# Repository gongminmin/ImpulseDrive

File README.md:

# Impulse Drive

In Star Trek universe, impulse drive is a propulsion system of spacecrafts for interplanetary travel. This project is trying to design a real-world impulse drive. The basic characteristics of this engine are

* Electric propulsion
* Large thrust
* Long specific impulse
* No or little moving parts
* Good scalability
* Low cost

We'd like to make it easy to implement, so people can build it as a hobby project.

NOTE: Please turn on git LFS when cloning this project.

## Method

There are many different engine designs for spacecraft propulsion, check [wikipedia](https://en.wikipedia.org/wiki/Spacecraft_propulsion#Table_of_methods) for a list. The only one design among them that fits these requirements is magnetoplasmadynamic thruster, a.k.a, MPDT or MPD thruster. More details in [MPD](Doc/Mpd.md).

Our design is based on MPDT, with several significant improvements.

## Design

The principle of our design, and a detailed introduction of modules are in [Design](Doc/Design.md)

## Disclaimer

MPD thruster is operated by **LETHALLY** high voltage and current. If you don't have enough knowledge and experiences on high voltage electric, please keep extreme cautions on insulation.

## Directories

* Circuit folder is the electric design of the system. The files can be open by [KiCad](https://kicad-pcb.org/)
* 3DModel folder is the 3D model design of some components. It's in [Blender](https://www.blender.org/) format.
* Doc folder contains some documents

## License

ImpulseDrive is distributed under the terms of MIT License. See [LICENSE](LICENSE) for details.

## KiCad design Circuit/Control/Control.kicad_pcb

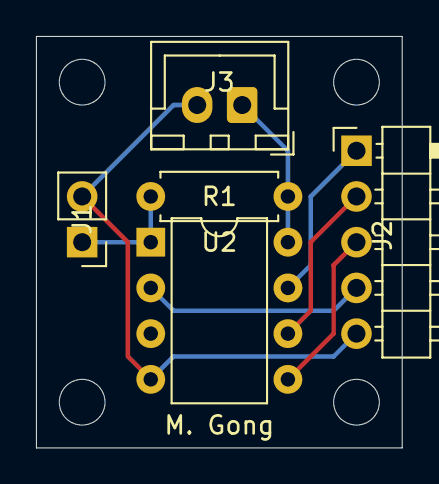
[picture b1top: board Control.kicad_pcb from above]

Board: 2 copper layers, 20.3 x 22.9 mm, 5 parts (0 on the bottom side), 7 nets.

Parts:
J1: Signal; PinHeader_1x02_P2.54mm_Vertical
J2: To Switch; PinHeader_1x05_P2.54mm_Horizontal
J3: Power; JST_XH_B2B-XH-A_1x02_P2.50mm_Vertical
R1: 3.3K; R_Axial_DIN0207_L6.3mm_D2.5mm_P7.62mm_Horizontal
U2: ATtiny85-20PU; DIP-8_W7.62mm

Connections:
+5V: J3.1, R1.1, U2.8
/CapacitorSignal: J2.4, U2.2
/CoilSignal: J2.1, U2.7
/ControlSignal: J1.1, R1.2, U2.1
/PropellantInjectorSignal: J2.3, U2.5
/StarterSignal: J2.2, U2.6
GND: J1.2, J2.5, J3.2, U2.4

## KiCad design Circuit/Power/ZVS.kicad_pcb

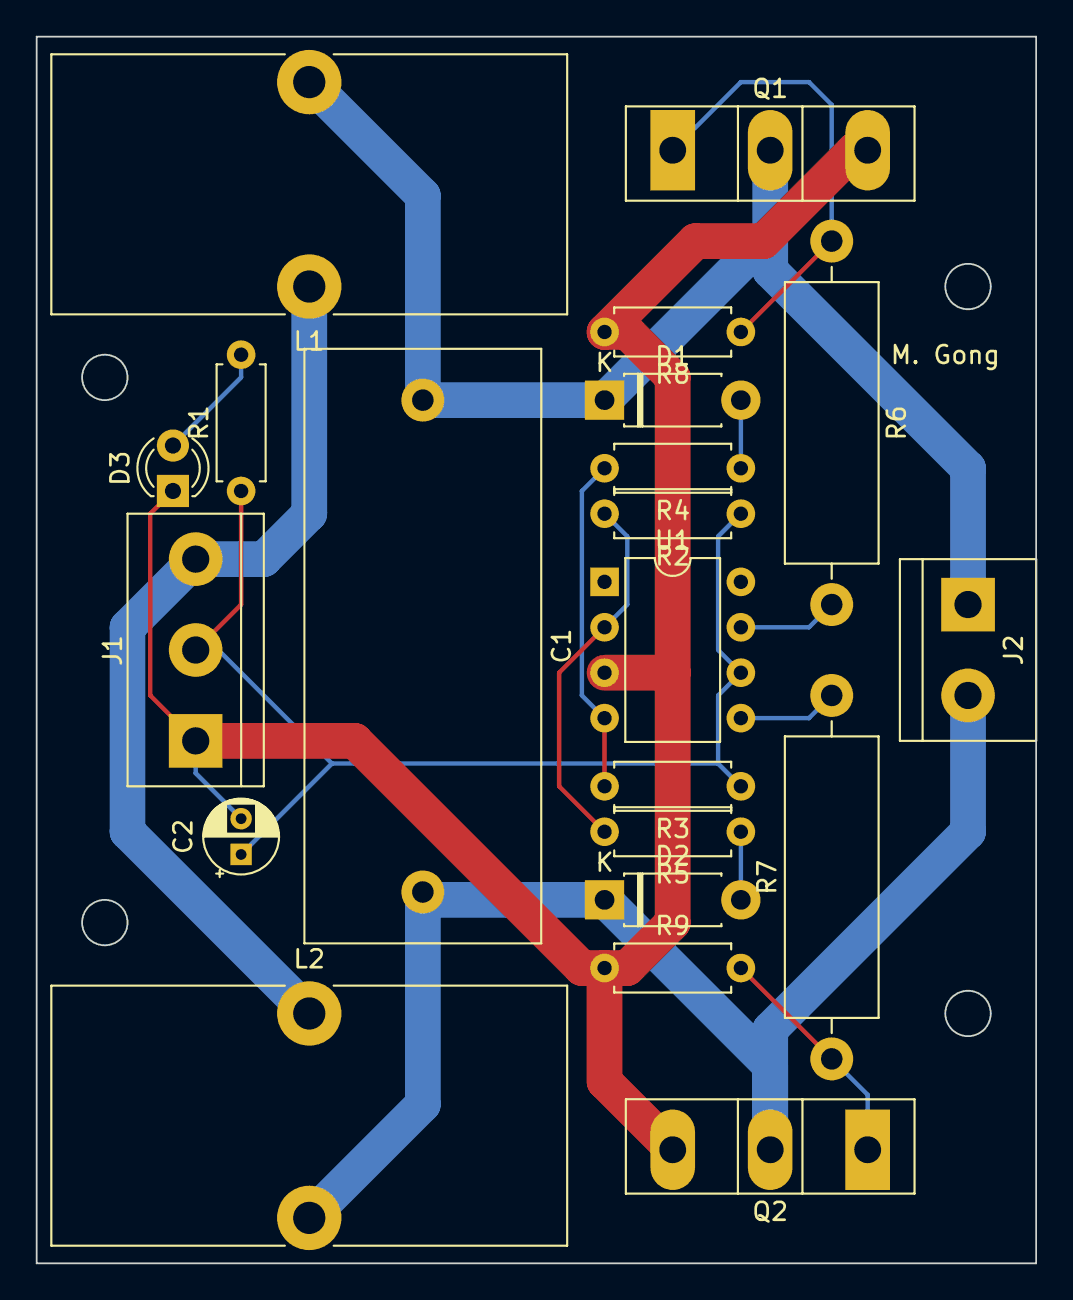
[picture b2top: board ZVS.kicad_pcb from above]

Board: 2 copper layers, 55.9 x 68.6 mm, 21 parts (0 on the bottom side), 14 nets.

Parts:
C1: MKP 0.33uF; C_Rect_L33.0mm_W13.0mm_P27.50mm_MKS4
C2: 10uF; CP_Radial_D4.0mm_P2.00mm
D1, D2: UF4007; D_DO-41_SOD81_P7.62mm_Horizontal
D3: LED; LED_D3.0mm_FlatTop
J1: 12V DC in; TerminalBlock_bornier-3_P5.08mm
J2: Output; TerminalBlock_bornier-2_P5.08mm
L1, L2: 100uH; L_Toroid_Vertical_L28.6mm_W14.3mm_P11.43mm_Bourns_5700
Q1, Q2: IRFP250; TO-247-3_Vertical
R1: 2.2K; R_Axial_DIN0207_L6.3mm_D2.5mm_P7.62mm_Horizontal
R2, R3: 3.3K; R_Axial_DIN0207_L6.3mm_D2.5mm_P7.62mm_Horizontal
R4, R5: 100; R_Axial_DIN0207_L6.3mm_D2.5mm_P7.62mm_Horizontal
R6, R7: 10R 5W; R_Axial_DIN0516_L15.5mm_D5.0mm_P20.32mm_Horizontal
R8, R9: 10K; R_Axial_DIN0207_L6.3mm_D2.5mm_P7.62mm_Horizontal
U1: UCC27524P; DIP-8_W7.62mm

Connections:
/DCInput+: C2.1, J1.2, R1.1, R2.1, R3.1, U1.6
/Output+: C1.1, D1.1, J2.1, L1.2, Q1.2
/Output-: C1.2, D2.1, J2.2, L2.2, Q2.2
GND: C2.2, D3.1, J1.1, Q1.3, Q2.3, R8.2, R9.1, U1.3
unnamed: D1.2, R4.1
unnamed: D2.2, R5.1
unnamed: D3.2, R1.2
unnamed: J1.3, L1.1, L2.1
unnamed: Q1.1, R6.1, R8.1
unnamed: Q2.1, R7.1, R9.2
unnamed: R2.2, R5.2, U1.2
unnamed: R3.2, R4.2, U1.4
unnamed: R6.2, U1.7
unnamed: R7.2, U1.5

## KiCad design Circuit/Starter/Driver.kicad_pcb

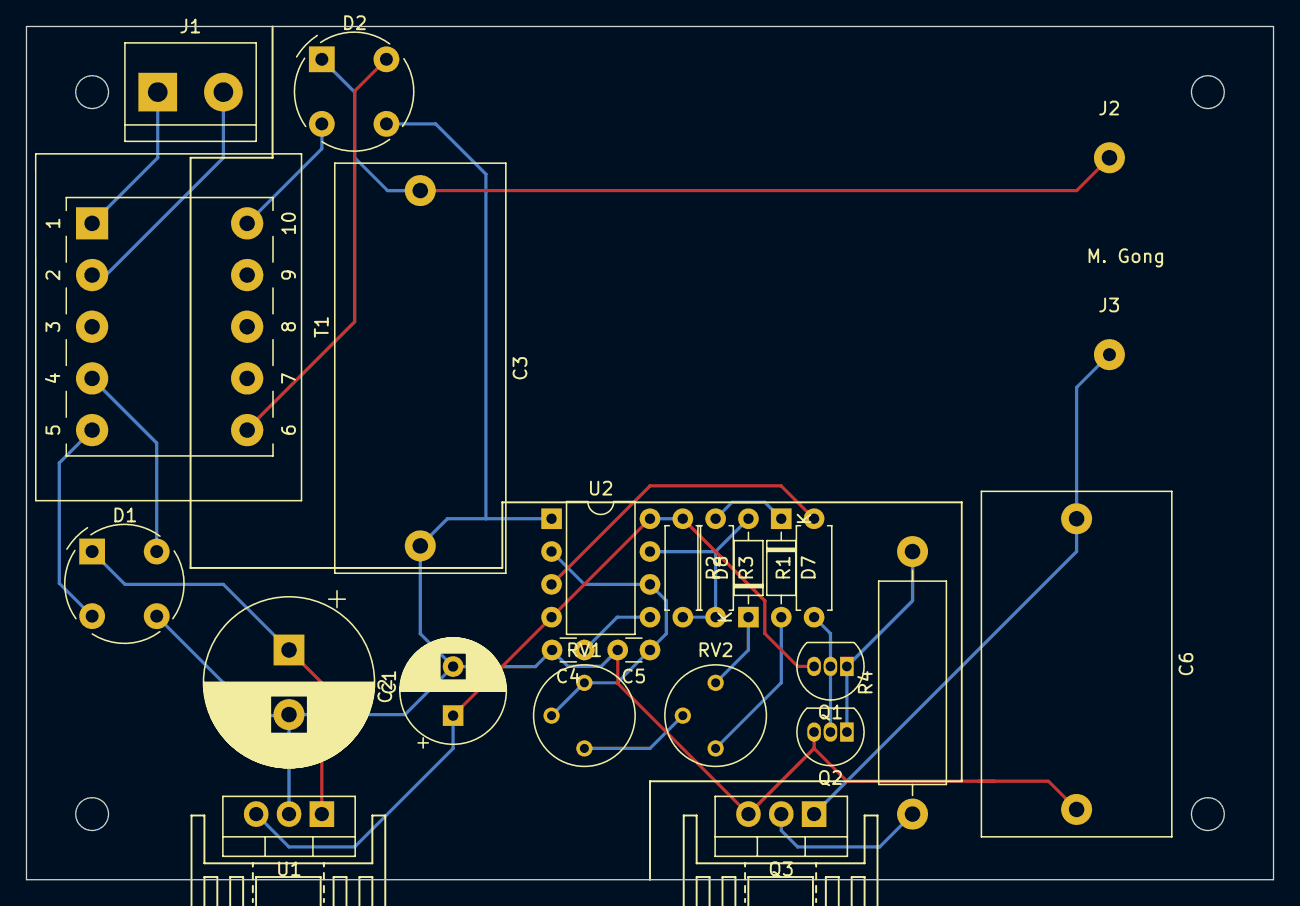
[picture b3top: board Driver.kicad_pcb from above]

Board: 2 copper layers, 96.5 x 66.0 mm, 27 parts (0 on the bottom side), 22 nets.

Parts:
C1: 2200uF; CP_Radial_D13.0mm_P5.00mm
C2: 1000uF; CP_Radial_D8.0mm_P3.80mm
C3: MKP 1uF 275V; C_Rect_L31.5mm_W13.0mm_P27.50mm_MKS4
C4: 0.01uF; C_Disc_D3.0mm_W1.6mm_P2.50mm
C5: 330pF; C_Disc_D3.0mm_W1.6mm_P2.50mm
C6: 0.01uF 2kV; C_Rect_L26.5mm_W15mm_P22.50mm_MKS4
D1, D2: 2W10; Diode_Bridge_Round_D9.0mm
D7, D8: 1N4148; D_DO-35_SOD27_P7.62mm_Horizontal
HS1, HS2: Heatsink; Heatsink_TO220_15x10mm
J1: AC Power; TerminalBlock_bornier-2_P5.08mm
J2: To Output Transformer+; SolderWirePad_1x01_Drill1.2mm
J3: To Output Transformer-; SolderWirePad_1x01_Drill1.2mm
Q1: 2N3904; TO-92_Inline
Q2: 2N3906; TO-92_Inline
Q3: FCPF220N80; TO-220-3_Vertical
R1: 270; R_Axial_DIN0207_L6.3mm_D2.5mm_P7.62mm_Horizontal
R2, R3: 1K; R_Axial_DIN0207_L6.3mm_D2.5mm_P7.62mm_Horizontal
R4: 10R 5W; R_Axial_DIN0516_L15.5mm_D5.0mm_P20.32mm_Horizontal
RV1, RV2: 5K; Potentiometer_Bourns_3339P_Vertical
T1: 6:6:50; Transformer_Generic_EE25_10Pin
U1: L7812; TO-220-3_Vertical
U2: NE555; DIP-8_W7.62mm

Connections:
+12V: C2.1, Q1.3, R2.1, U1.3, U2.4, U2.8
/PowerIn+: J1.1, T1.1
/PowerIn-: J1.2, T1.2
/ToOutputTransformer+: C3.1, D2.1, J2.1
/ToOutputTransformer-: C6.1, J3.1, Q3.1
GND: C1.2, C2.2, C3.2, C4.2, C5.2, C6.2, D1.3, D2.3, Q2.3, Q3.3, U1.2, U2.1
unnamed: C1.1, D1.1, U1.1
unnamed: C4.1, U2.5
unnamed: C5.1, RV1.2, RV1.3, U2.2, U2.6
unnamed: D1.2, T1.5
unnamed: D1.4, T1.4
unnamed: D2.2, T1.10
unnamed: D2.4, T1.6
unnamed: D7.1, R3.1
unnamed: D7.2, RV2.1
unnamed: D8.1, RV2.3
unnamed: D8.2, R2.2, R3.2, U2.7
unnamed: Q1.1, Q2.1, R4.2
unnamed: Q1.2, Q2.2, R1.1
unnamed: Q3.2, R4.1
unnamed: R1.2, U2.3
unnamed: RV1.1, RV2.2

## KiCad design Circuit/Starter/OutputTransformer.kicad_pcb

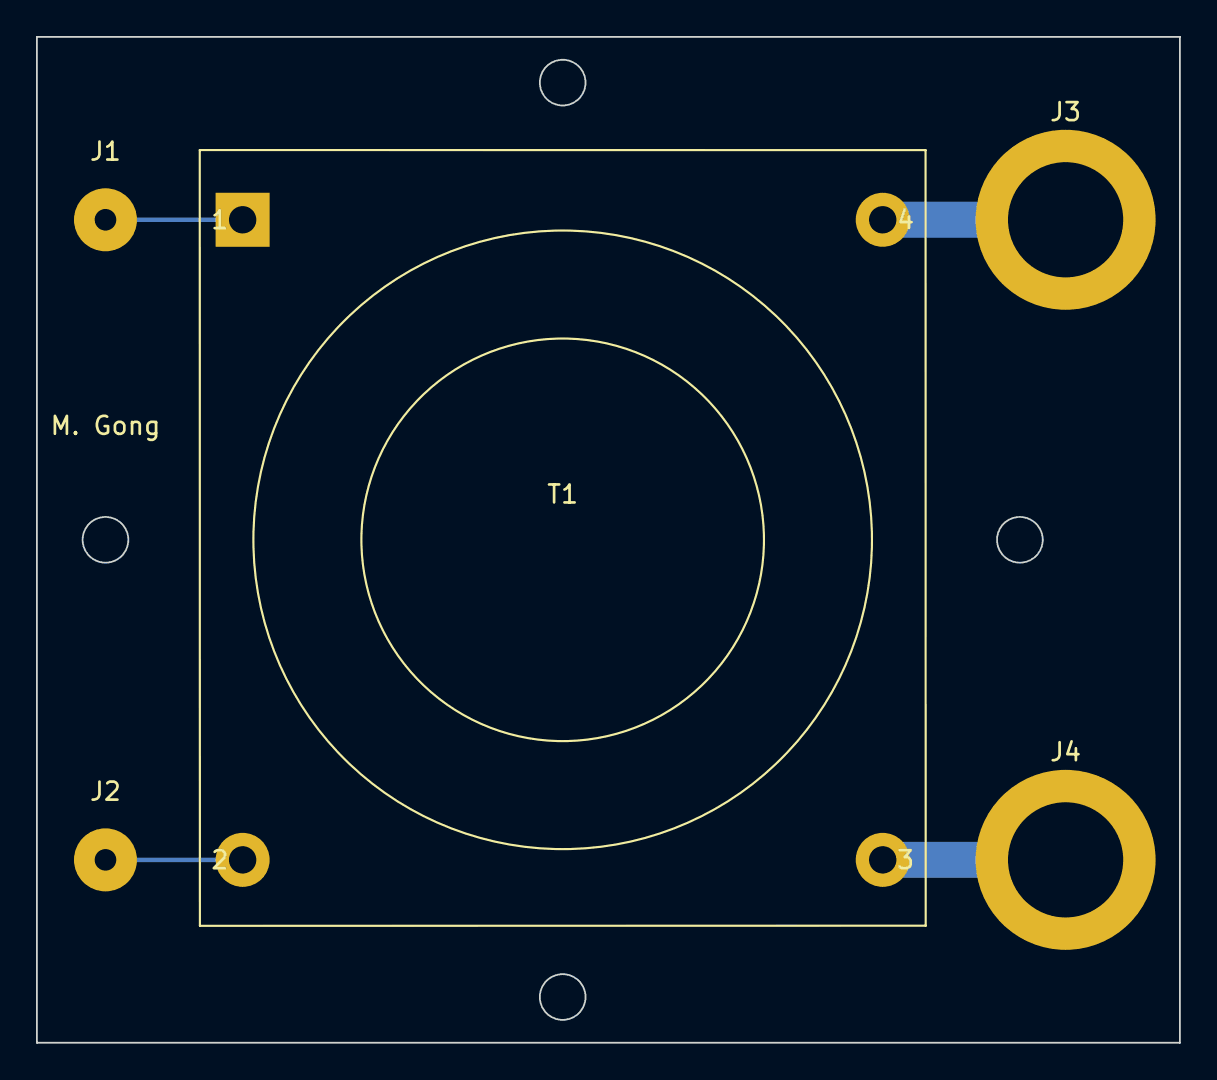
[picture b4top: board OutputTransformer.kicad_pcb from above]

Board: 2 copper layers, 63.5 x 55.9 mm, 5 parts (0 on the bottom side), 4 nets.

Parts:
J1: Input+; SolderWirePad_1x01_Drill1.2mm
J2: Input-; SolderWirePad_1x01_Drill1.2mm
J3: Output+; MountingHole_6.4mm_M6_ISO14580_Pad
J4: Output-; MountingHole_6.4mm_M6_ISO14580_Pad
T1: 3:40 Air Core (primary 0.8uH, 0.225in length, 2in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; Air_Core_Transformer_Vertical_1P_1S

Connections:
/Input+: J1.1, T1.1
/Input-: J2.1, T1.2
/Output+: J3.1, T1.4
/Output-: J4.1, T1.3

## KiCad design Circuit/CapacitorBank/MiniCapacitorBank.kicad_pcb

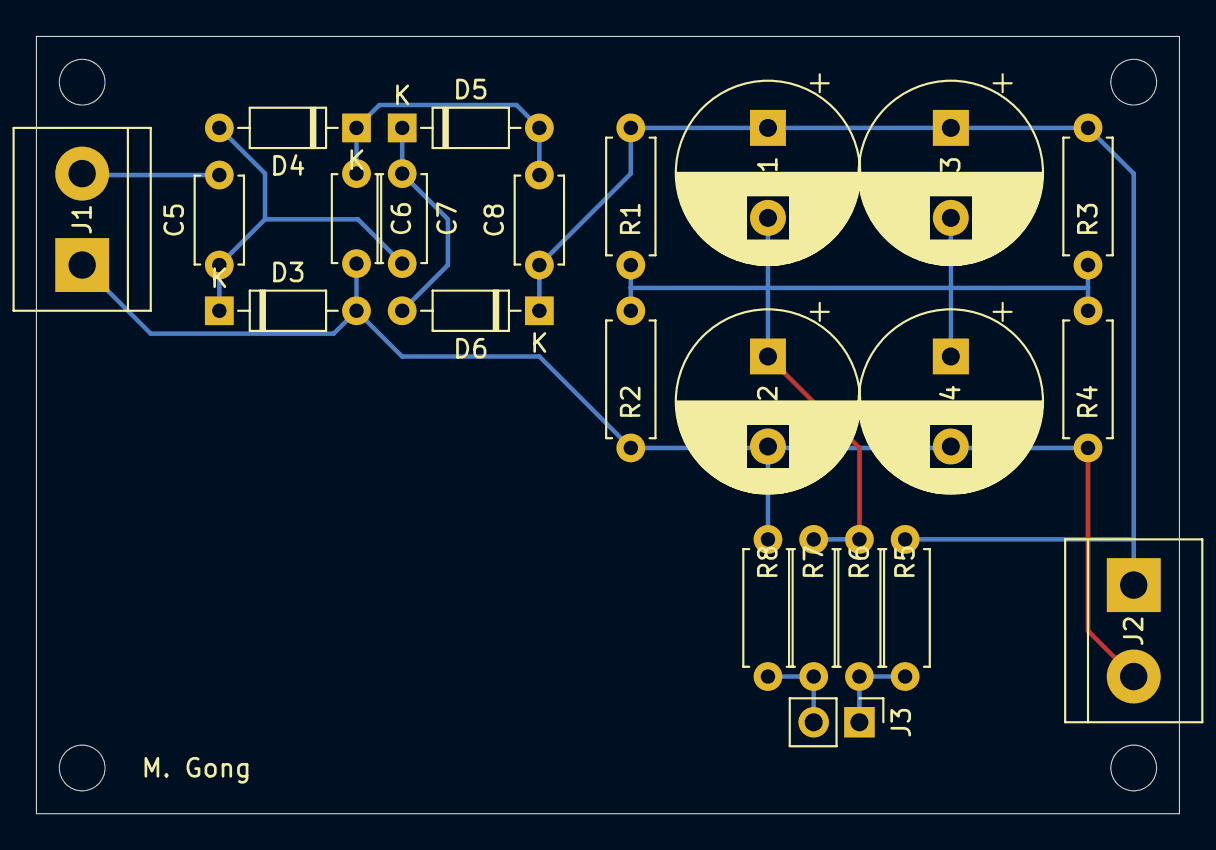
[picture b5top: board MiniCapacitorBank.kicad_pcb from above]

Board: 2 copper layers, 63.5 x 43.2 mm, 23 parts (0 on the bottom side), 9 nets.

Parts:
C1, C2, C3, C4: 330uF/50V; CP_Radial_D10.0mm_P5.00mm
C5, C6, C7, C8: 0.1uF; C_Disc_D4.7mm_W2.5mm_P5.00mm
D3, D4, D5, D6: 1N4148; D_DO-35_SOD27_P7.62mm_Horizontal
J1: AC Power In; TerminalBlock_bornier-2_P5.08mm
J2: 68V out; TerminalBlock_bornier-2_P5.08mm
J3: To Voltage Sensing; PinHeader_1x02_P2.54mm_Vertical
R1, R2, R3, R4: 68K; R_Axial_DIN0207_L6.3mm_D2.5mm_P7.62mm_Horizontal
R5, R8: 1M; R_Axial_DIN0207_L6.3mm_D2.5mm_P7.62mm_Horizontal
R6, R7: 100K; R_Axial_DIN0207_L6.3mm_D2.5mm_P7.62mm_Horizontal

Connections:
/ACPowerIn+: C5.2, J1.2
/ACPowerIn-: C2.2, C4.2, C6.2, D3.2, J1.1, J2.2, R2.2, R4.2, R8.2
/PowerOut+: C1.1, C3.1, C8.1, D6.1, J2.1, R1.1, R3.1, R5.1
/Sensor0V: J3.2, R7.2, R8.1
/Sensor6V: J3.1, R5.2, R6.1
unnamed: C1.2, C2.1, C3.2, C4.1, R1.2, R2.1, R3.2, R4.1, R6.2, R7.1
unnamed: C5.1, C7.2, D3.1, D4.2
unnamed: C6.1, C8.2, D4.1, D5.2
unnamed: C7.1, D5.1, D6.2

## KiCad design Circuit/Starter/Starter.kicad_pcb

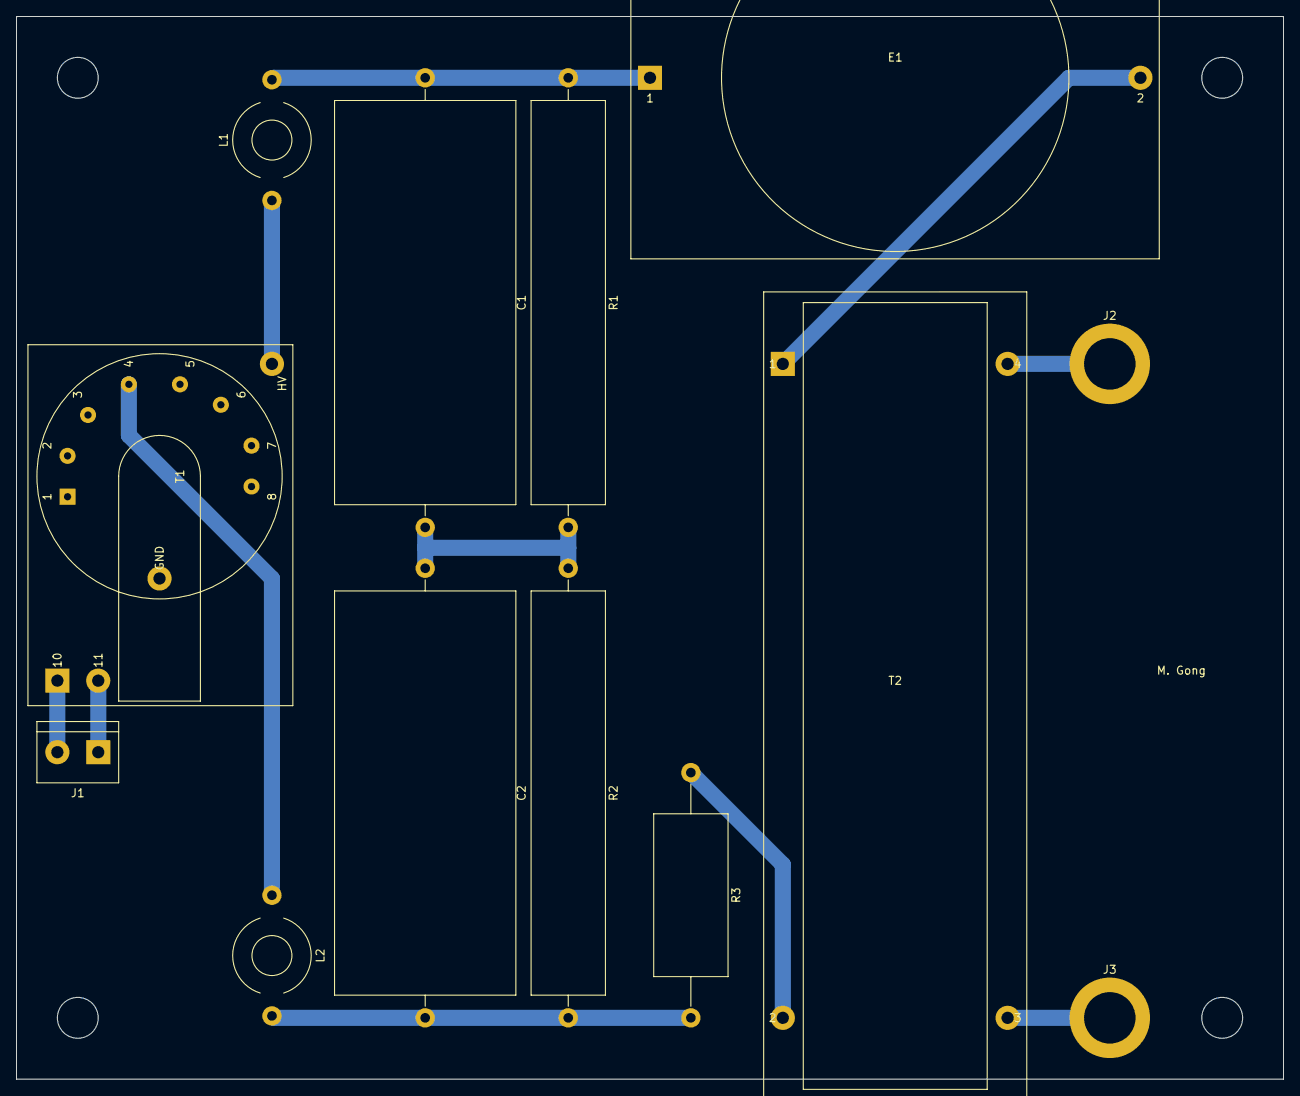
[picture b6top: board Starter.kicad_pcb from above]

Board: 2 copper layers, 157.5 x 132.1 mm, 13 parts (0 on the bottom side), 11 nets.

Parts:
C1, C2: 10nF/8kV; C_Axial_L50.0mm_D23.0mm_P55.0mm_Horizontal
E1: SPARK_GAP 10kV; Spark_Gap
J1: From Power; TerminalBlock_bornier-2_P5.08mm
J2: Output+; MountingHole_6.4mm_M6_ISO14580_Pad
J3: Output-; MountingHole_6.4mm_M6_ISO14580_Pad
L1, L2: 10uH; L_Toroid_Horizontal_D9.5mm_P15.00mm_Diameter10-5mm_Amidon-T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
R1, R2: 100M/5W; R_Axial_Power_L50.0mm_W9.0mm_P55.88mm
R3: 1Ω/10W; R_Axial_DIN0922_L20.0mm_D9.0mm_P30.48mm_Horizontal
T1: BSH12-N406L 8:6400; Flyback_Transformer_BSH12-N406L
T2: 20:20; Air_Core_Transformer_1P_1S

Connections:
/PowerIn+: J1.2, T1.10
/PowerIn-: J1.1, T1.11
/PowerOut+: J2.1, T2.4
/PowerOut-: J3.1, T2.3
unnamed: C1.1, E1.1, L1.2, R1.1
unnamed: C1.2, C2.1, R1.2, R2.1
unnamed: C2.2, L2.2, R2.2, R3.2
unnamed: E1.2, T2.1
unnamed: L1.1, T1.12
unnamed: L2.1, T1.4
unnamed: R3.1, T2.2

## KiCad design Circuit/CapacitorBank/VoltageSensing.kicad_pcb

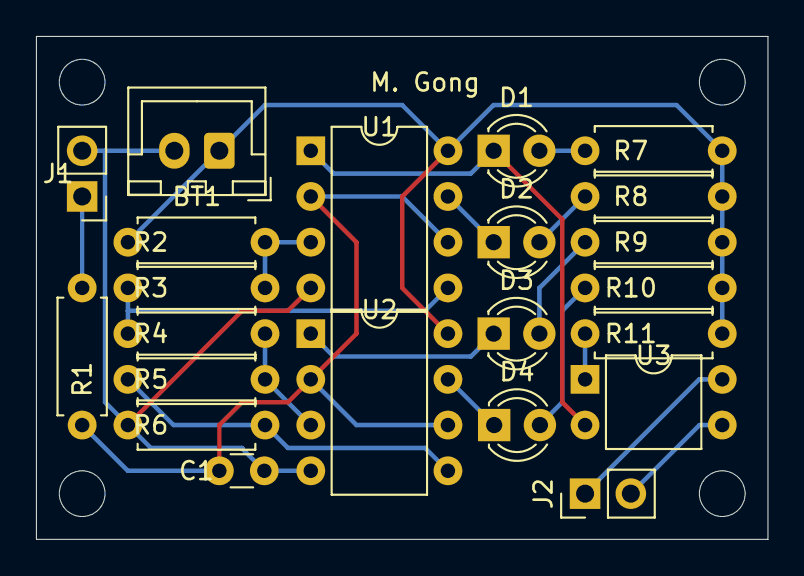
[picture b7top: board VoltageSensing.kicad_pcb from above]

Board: 2 copper layers, 40.6 x 27.9 mm, 22 parts (0 on the bottom side), 19 nets.

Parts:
BT1: 12V Battery; JST_XH_B2B-XH-A_1x02_P2.50mm_Vertical
C1: 0.1uF; C_Disc_D3.0mm_W1.6mm_P2.50mm
D1, D2, D3, D4: LED; LED_D3.0mm_FlatTop
J1: From Capacitor Bank; PinHeader_1x02_P2.54mm_Vertical
J2: To Control; PinHeader_1x02_P2.54mm_Vertical
R1, R11: 1K; R_Axial_DIN0207_L6.3mm_D2.5mm_P7.62mm_Horizontal
R2: 20K; R_Axial_DIN0207_L6.3mm_D2.5mm_P7.62mm_Horizontal
R3, R4, R5, R6: 4.7K; R_Axial_DIN0207_L6.3mm_D2.5mm_P7.62mm_Horizontal
R7, R8, R9, R10: 2.2K; R_Axial_DIN0207_L6.3mm_D2.5mm_P7.62mm_Horizontal
U1, U2: LM393; DIP-8_W7.62mm
U3: PC817; DIP-4_W7.62mm

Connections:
+12V: BT1.1, R2.2, R7.1, R8.1, R9.1, R10.1, R11.1, U1.8, U2.8
/ControlGND: J2.2, U3.3
/ControlSignal: J2.1, U3.4
/Sensor6V: J1.1, R1.2
GND: BT1.2, C1.2, J1.2, R6.1, U1.4, U2.4
unnamed: C1.1, R1.1, U1.2, U1.6, U2.2, U2.6
unnamed: D1.1, U1.1, U3.2
unnamed: D1.2, R7.2
unnamed: D2.1, U1.7
unnamed: D2.2, R8.2
unnamed: D3.1, U2.1
unnamed: D3.2, R9.2
unnamed: D4.1, U2.7
unnamed: D4.2, R10.2
unnamed: R2.1, R3.2, U1.3
unnamed: R3.1, R4.2, U1.5
unnamed: R4.1, R5.2, U2.3
unnamed: R5.1, R6.2, U2.5
unnamed: R11.2, U3.1

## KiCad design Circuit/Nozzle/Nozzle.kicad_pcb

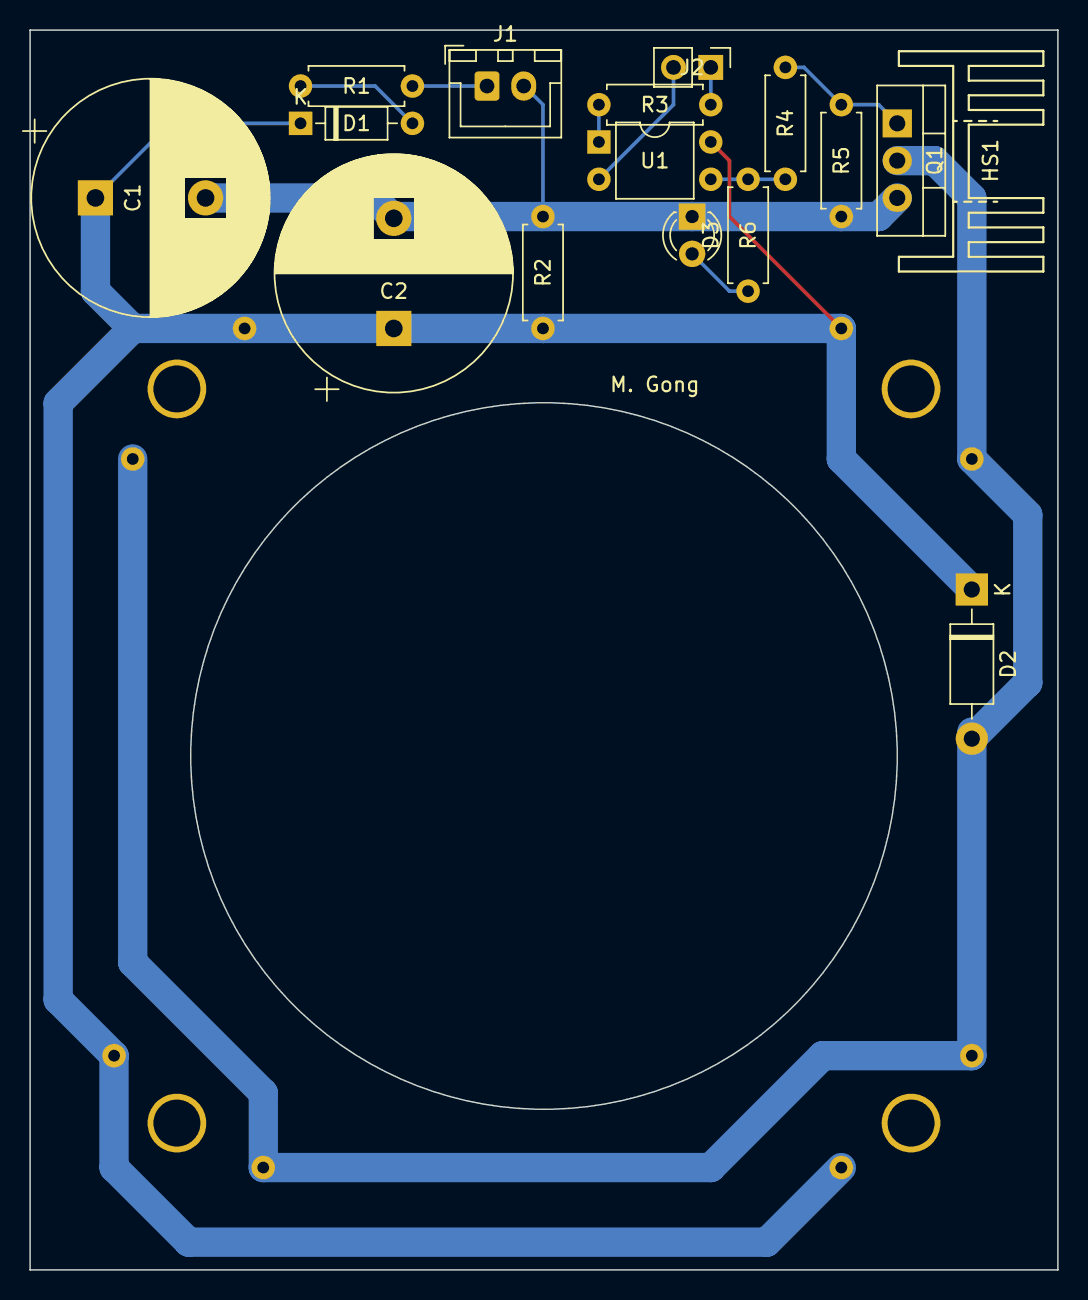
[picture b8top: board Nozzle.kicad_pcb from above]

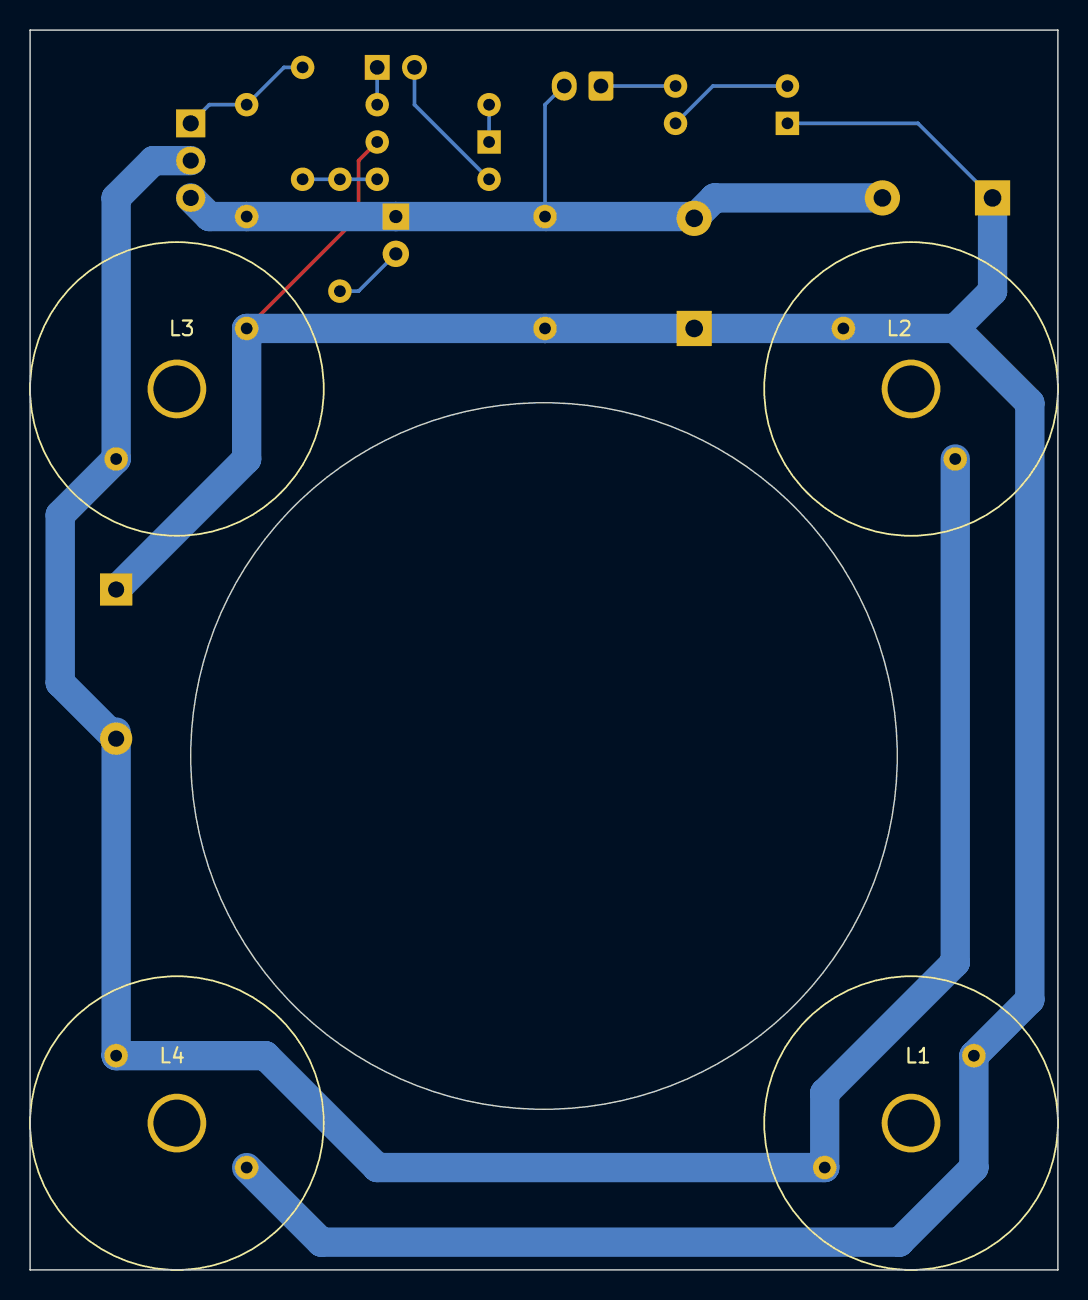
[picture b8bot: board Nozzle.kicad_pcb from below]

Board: 2 copper layers, 70.0 x 84.4 mm, 20 parts (4 on the bottom side), 11 nets.

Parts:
C1, C2: 4700uF; CP_Radial_D16.0mm_P7.50mm
D1: 1N4148; D_DO-35_SOD27_P7.62mm_Horizontal
D2: 1N4007; D_DO-41_SOD81_P10.16mm_Horizontal
D3: LED; LED_D3.0mm_FlatTop
HS1: Heatsink; Heatsink_TO220_15x10mm
J1: Coil Power; JST_XH_B2B-XH-A_1x02_P2.50mm_Vertical
J2: CoilSignal; PinHeader_1x02_P2.54mm_Vertical
L1, L2, L3, L4: Electromagnetic; Electromagnet
Q1: RFP30N06LE; TO-220-3_Vertical
R1: 220; R_Axial_DIN0207_L6.3mm_D2.5mm_P7.62mm_Horizontal
R2: 5.1K; R_Axial_DIN0207_L6.3mm_D2.5mm_P7.62mm_Horizontal
R3: 680; R_Axial_DIN0207_L6.3mm_D2.5mm_P7.62mm_Horizontal
R4: 4.7K; R_Axial_DIN0207_L6.3mm_D2.5mm_P7.62mm_Horizontal
R5: 10K; R_Axial_DIN0207_L6.3mm_D2.5mm_P7.62mm_Horizontal
R6: 2.2K; R_Axial_DIN0207_L6.3mm_D2.5mm_P7.62mm_Horizontal
U1: PC817; DIP-4_W7.62mm

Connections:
/CoilPower+: J1.1, R1.2
/CoilPower-: C1.2, C2.2, D3.1, J1.2, Q1.3, R2.2, R5.2
/CoilSignal+: J2.1, R3.2
/CoilSignal-: J2.2, U1.2
unnamed: C1.1, C2.1, D1.1, D2.1, L1.1, L2.1, L3.1, L4.1, R2.1, U1.4
unnamed: D1.2, R1.1
unnamed: D2.2, L1.2, L2.2, L3.2, L4.2, Q1.2
unnamed: D3.2, R6.2
unnamed: Q1.1, R4.1, R5.1
unnamed: R3.1, U1.1
unnamed: R4.2, R6.1, U1.3

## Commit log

2020-10-09 [Circuit] Add basic modules
2020-10-09 [Circuit] Move the Nozzle's MOSFET to power module
2020-10-09 [Circuit] Add customized footprint and symbol for transformers
2020-10-09 [Circuit] More accurate on the dimension of transformers
2020-10-09 [Circuit] Add ZVS module
2020-10-09 [Circuit] Use MOSFETs instead of TRIACs to control the powers
2020-10-09 [Circuit] Use a single 12V power for control module
2020-10-09 [Circuit] Optimize the PCB of power module
2020-10-09 [Circuit] Change the isolation transformer to a toroid one
2020-10-09 [Circuit] Add details to starter module
2020-10-09 [Circuit] Add a 1-stage Cockcroft–Walton generator to power module
2020-10-09 [Doc] Add some documents
2020-10-09 [Circuit] Merge Bleeder into CapacitorBank module
2020-10-09 [Doc] Add detailed introduction of power module
2020-10-09 [Engineering] Turn on LFS
2020-10-09 [Circuit] Move transformers from Power to other circuit diagrams
2020-10-09 [Circuit] Add propellant injector into the overall circuit
2020-10-09 [Engineering] Move circuit specific gitignore to its folder
2020-10-09 [Circuit] Move ControlTester to Control folder
2020-10-09 [Doc] Add detailed introduction of control module
2020-10-09 [Circuit] Add a tester board for power switch
2020-10-09 [Doc] Add details and diagrams to design document
2020-10-09 [Doc] Add detailed introduction of propellant injector
2020-10-09 [Model] Add 3D models for nozzle components
2020-10-09 [Circuit] Polarized capacitor bank and bleeder
2020-10-09 [Doc] Add detailed introduction of nozzle
2020-10-09 [Circuit] Optimize the switch tester's PCB
2020-10-09 [Doc] Add detailed introduction of starter module
2020-10-09 [Doc] Fix typos
2020-10-09 [Doc] Add calculations about discharge time
2020-10-09 [Doc] Add detailed introduction of capacitor bank module
2020-10-09 [Doc] Add photos of starter module components
2020-10-09 [Circuit] Add bleeder resistors to Starter
2020-10-09 [Circuit] Add PCB design for starter
2020-10-09 [Doc] Add safety instructions
2020-10-09 [Circuit] Optimize circuit diagrams
2020-10-09 [Doc] Add charging time calculation
2020-10-09 [Circuit] Change pin names
2020-10-09 [Circuit] Optimizations on PCB layouts
2020-10-09 [Circuit] Separate voltage sensing part into its own schematic
2020-10-09 [Circuit] Add a separated battery for Control module
2020-10-09 [Doc] Add doc about voltage sensing circuit
2020-10-09 [Circuit] Refactor on capacitor bank schematic
    1. Move voltage divider to capacitor bank schematic
    2. Merge mini and full voltage sensing schematics
    3. Add voltage followers
2020-10-09 [Circuit] Update the turns of transformers
2020-10-09 [Doc] Redefine module to subsystem, part to module
2020-10-09 [Doc] Add more calculations to get the accurate numbers
2020-10-09 [Circuit] Update the numbers in capacitor bank subsystem
2020-10-09 [Circuit] Add mini converter module for mini capacitor bank
2020-10-09 [Circuit] Improve the mini converter a little bit
2020-10-09 [Doc] Improve the doc of capacitor bank
2020-10-09 [Doc] Add more details about transformers
2020-10-09 [Circuit] Optimize the layout of PCBs of capacitor banks
2020-10-09 [Circuit] Use full bridge rectifier instead of center tapped rectifier in starter
2020-10-09 [Circuit] Merge capacitor bank, converter, and bleeder circuits into one
2020-10-09 [Circuit] Add isolated switches to bleeder circuits
2020-10-09 [Circuit] Add a PCB design of ZVS module
2020-10-09 [Circuit] Rename the flyback transformer file
2020-10-09 [Circuit] Optimize PCBs
2020-10-09 [Circuit] Move the flyback diode from nozzle to switch module
2020-10-09 [Doc] Add photo of the assembled nozzle
2020-10-09 [Circuit] Optimize the layout of PCBs
2020-10-09 [Doc] Refine some words in design
2020-10-09 [Circuit] Add switch adapter circuit
2020-10-09 [Circuit] Major redesign on the switch module using self-powered solid state relay
2020-10-09 [Circuit] Add DC relay design
2020-10-09 [Circuit] Fine tune some pcb layouts
2020-10-09 [Circuit] Merge switch adapter and relays into one board
2020-10-09 [Circuit] Adjust the position of components in switch module
2020-10-09 [Circuit] Fix the direction of diode in starter
2020-10-09 [Circuit] Adjust the sizes of components to reflect the real ones
2020-10-09 [Circuit] Adjust the resistors in capacitor bank, again
2020-10-09 [Circuit] Adjust resistors in capacitor bank
2020-10-09 [Circuit] One channel voltage sensing and control modules
2020-10-09 [Circuit] Adjust footprint of customized components and optimize the PCB design
2020-10-09 [Circuit] Enable to export gerber files
2020-10-09 [Circuit] Add a discharge signal to capacitor bank
2020-10-09 [Circuit] Add screw holes to PCBs
2020-10-09 [Circuit] Shorten the lines in switch module diagram
2020-10-09 [Circuit] Adjustable delay in control module
2020-10-09 [Doc] Update diagrams and add calculations in starter subsystem
2020-10-09 [Circuit] Optimize the interface between capacitor bank modules and voltage sensing module
2020-10-09 [Circuit] Chage the triacs from BT138-800 to BTA208X-1000C
2020-10-09 [Circuit] Adjust some resistors
2020-10-09 [Circuit] Fix the connections around triac
2020-10-09 [Circuit] Update the control test module to use on the new control module
2020-10-09 [Circuit] Add voltage sensing tester module
2020-10-09 [Circuit] Refine the control module
2020-10-09 [Circuit] Remove quirk dischargers from capacitor bank
2020-10-09 [Circuit] Dual inductor variety of the ZVS module
2020-10-09 [Circuit] Simplify the resistors in capacitor bank
2020-10-09 [Circuit] Change the interface between control module, switch module, and discharge signal
2020-10-09 [Circuit] Optimize the PCB of control module
2020-10-09 [Circuit] Fix a couple issues
2020-10-09 [Circuit] Fix the resistors in voltage sensing module
2020-10-09 [Circuit] Add propellant injector signal
2020-10-09 [Circuit] Add real propellant injector control
2020-10-09 [Circuit] Update the control tester to reflect the changes of control module
2020-10-09 [Circuit] Change the decoupling capacitors to a larger ones
2020-10-09 [Circuit] Add a bypass diode to capacitor bank adapter for safety
2020-10-09 [Circuit] Merge voltage sensing into full capacitor bank to form a adapter module
2020-10-09 [Circuit] Rename the transformer in ZVS from 5pin to 4pin
2020-10-09 [Circuit] Remove fp-lib-table from gitignore
2020-10-09 [Circuit] Optimize the PCB layout of the capacitor bank adapter
2020-10-09 [Model] New nozzle case design with 0.5'' pipes
2020-10-09 [Circuit] Add mini capacitor bank to the CapacitorBank schema
2020-10-09 [Circuit] Use M6 bolt as the connectors of capacitor bank and starter
2020-10-09 [Model] Adjust the materials of nozzle case
2020-10-09 [Model] Update the model of coil
2020-10-09 [Model] Simplify the model of nozzle case, and add a pvc version of it
2020-10-09 [Model] Adjust the size of nozzle case models
2020-10-09 [Model] A new design of nozzle case model for 3D printing
2020-10-09 [Model] Adjust the size of nozzle case models, again
2020-10-09 [Model] Ignore stl format files
2020-10-09 [Circuit] Remove a current limiting resistor from mini capacitor bank
2020-10-09 [Doc] Change the full voltage of mini capacitor bank to 50V, and add calculations of energy in capacitors [Circuit] Adjust a resistor to make it lit the top LED at ~50V
2020-10-10 [Doc] [Circuit] Restore the full voltage of mini capacitor bank to 68V
2020-10-14 [Doc] Describe the updated design of control subsystem, and its interface
2020-10-17 [Circuit] Move the region separators to F.SilkS layer
2020-10-17 [Doc] Fix a typo in control subsystem
2020-10-19 [Doc] Update the document of control subsystem
2020-10-19 [Circuit][Doc] Make the control module triggered by falling edge of the signal
2020-10-20 [Doc] Update the document of capacitor bank subsystem to reflect recent changes
2020-10-20 [Circuit][Doc] Remove the transformer from ZVS module
2020-10-20 [Doc] Update the document of power subsystem based on improvements to circuit
2020-10-20 [Circuit] Improve the PCB design of switch module
2020-10-20 [Circuit] Move the resistors on signal pins to switch module
2020-10-21 [Doc] Fix the trigger waveform, and highlight the falling edge
2020-10-21 [Circuit] Use 2 ZVS drivers to drive starter and capacitor bank, instead of switching the coils
2020-10-22 [Circuit] Rearrange the diagram of switch module
2020-10-25 [Doc] Update the document of power subsystem
2020-10-25 [Circuit] Move the flyback diode of electromagnet to nozzle PCB
2020-10-25 [Circuit] Add a circuit for propellant injector
2020-10-25 [Circuit] Remove the flyback diode from switch module so the PCB can be smaller
2020-10-25 [Circuit] Adjust the nozzle PCB
2020-10-27 [Circuit][Doc] Correct the voltage calculation in full capacitor bank adapter
2020-10-27 [Circuit] Fix the symbol of DC motor
2020-10-29 [Circuit] Use thick tracks in nozzle PCB
2020-11-16 [Circuit] Add a capacitor bank for EMs in nozzle
2020-11-17 [Circuit] Add protection components for EM board
2020-11-19 [Circuit] Adjust the resistors in mosfet SSRs
2020-11-21 [Circuit] Optimizations on switch module
2020-11-21 [Circuit] Use 2 big capacitors to replace 5 small ones
2020-11-21 [Circuit] Change the connector between control module and switch module
2020-12-04 [Circuit] Change the track width of nozzle module and switch module to allow larger current
2020-12-05 [Circuit] Optimize the pcb layout
2020-12-11 [Circuit] Add distribution module to power subsystem
2020-12-13 [Circuit] Change to smaller decoupling capacitors on distribution module
2020-12-13 [Circuit] Merge distribution module into switch module
2020-12-13 [Circuit] Add an LED indicator for power input
2020-12-13 [Circuit] Adjust the track width in ZVS module
2020-12-15 [Circuit] Fine tune the PCB of switch module
2020-12-20 [Circuit] Change the footprint of fuse holder based on the measurement
2020-12-21 [Circuit] Update the control tester circuit
2020-12-21 [Circuit] Use 5V power for control module
2020-12-25 [Circuit] Adjust the resistors to adapt to 5V control power
2020-12-25 [Circuit] Adjust the gate resistors
2021-01-26 [Circuit] Remove the full bridge from the output side of the starter, then change the capacitor bank to non-polarized configuration
2021-02-08 [Circuit] High frequency ZVS module with gate driver
2021-05-22 [Circuit] Remove the back-to-back capacitors from capacitor bank (again)
2021-05-22 [Circuit] Fix the reference of a resistor in starter module
2021-05-22 [Doc] Update the doc to reflect new changes in the design
2021-05-22 [Circuit] Start designing a solid state starter based on class-E Tesla coil
2021-05-22 [Circuit] A design to use ATtiny85 as a controller
2022-06-25 [Circuit] Update NE555 to P variety
2022-09-24 [Circuit] Upgrade to KiCad 6 format
